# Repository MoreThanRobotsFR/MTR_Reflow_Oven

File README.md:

# MTR Reflow Oven

**MTR Reflow Oven** is a comprehensive hardware and firmware project designed to control a reflow oven for PCB assembly. This repository contains the custom PCB design, the firmware for the RP2040 microcontroller, and a companion PC configurator tool.

## Repository Structure

*   **`Firmware/`**
    *   **`mtr_reflow_oven/`**: The core C++ firmware for the RP2040 microcontroller. It handles temperature PID control, user interface (LVGL), and profile management.
    *   **`Configurator/`**: A Python-based desktop application for creating and managing reflow profiles and configuring device settings.
*   **`Hardware/`**
    *   Contains the KiCad project files (`.kicad_pcb`, `.kicad_sch`) for the custom controller board.

## Getting Started

### Hardware
The `Hardware` directory contains the complete KiCad project. You can open `Hardware/MTR_Reflow_Oven.kicad_pro` with [KiCad 8.0+](https://www.kicad.org/) to view or modify the schematics and PCB layout.

### Firmware (RP2040)
The firmware is built using the Raspberry Pi Pico SDK.

**Prerequisites:**
*   CMake
*   Arm GNU Toolchain (`arm-none-eabi-gcc`)
*   Pico SDK

**Build Instructions:**
1.  Navigate to the firmware directory:
    ```bash
    cd Firmware/mtr_reflow_oven
    ```
2.  Create a build directory:
    ```bash
    mkdir build
    cd build
    ```
3.  Configure and build:
    ```bash
    cmake ..
    make
    ```
4.  Flash the resulting `.uf2` file to your RP2040 device.

### Configurator (PC Software)
The configurator allows you to easily edit reflow profiles.

**Prerequisites:**
*   Python 3.x
*   Required packages (see `requirements.txt` if available, or manually install common dependencies like `pyserial`, `tkinter`/`customtkinter`).

**Running:**
```bash
cd Firmware/Configurator
python reflow_configurator.py
```

## License
[License Information Here]

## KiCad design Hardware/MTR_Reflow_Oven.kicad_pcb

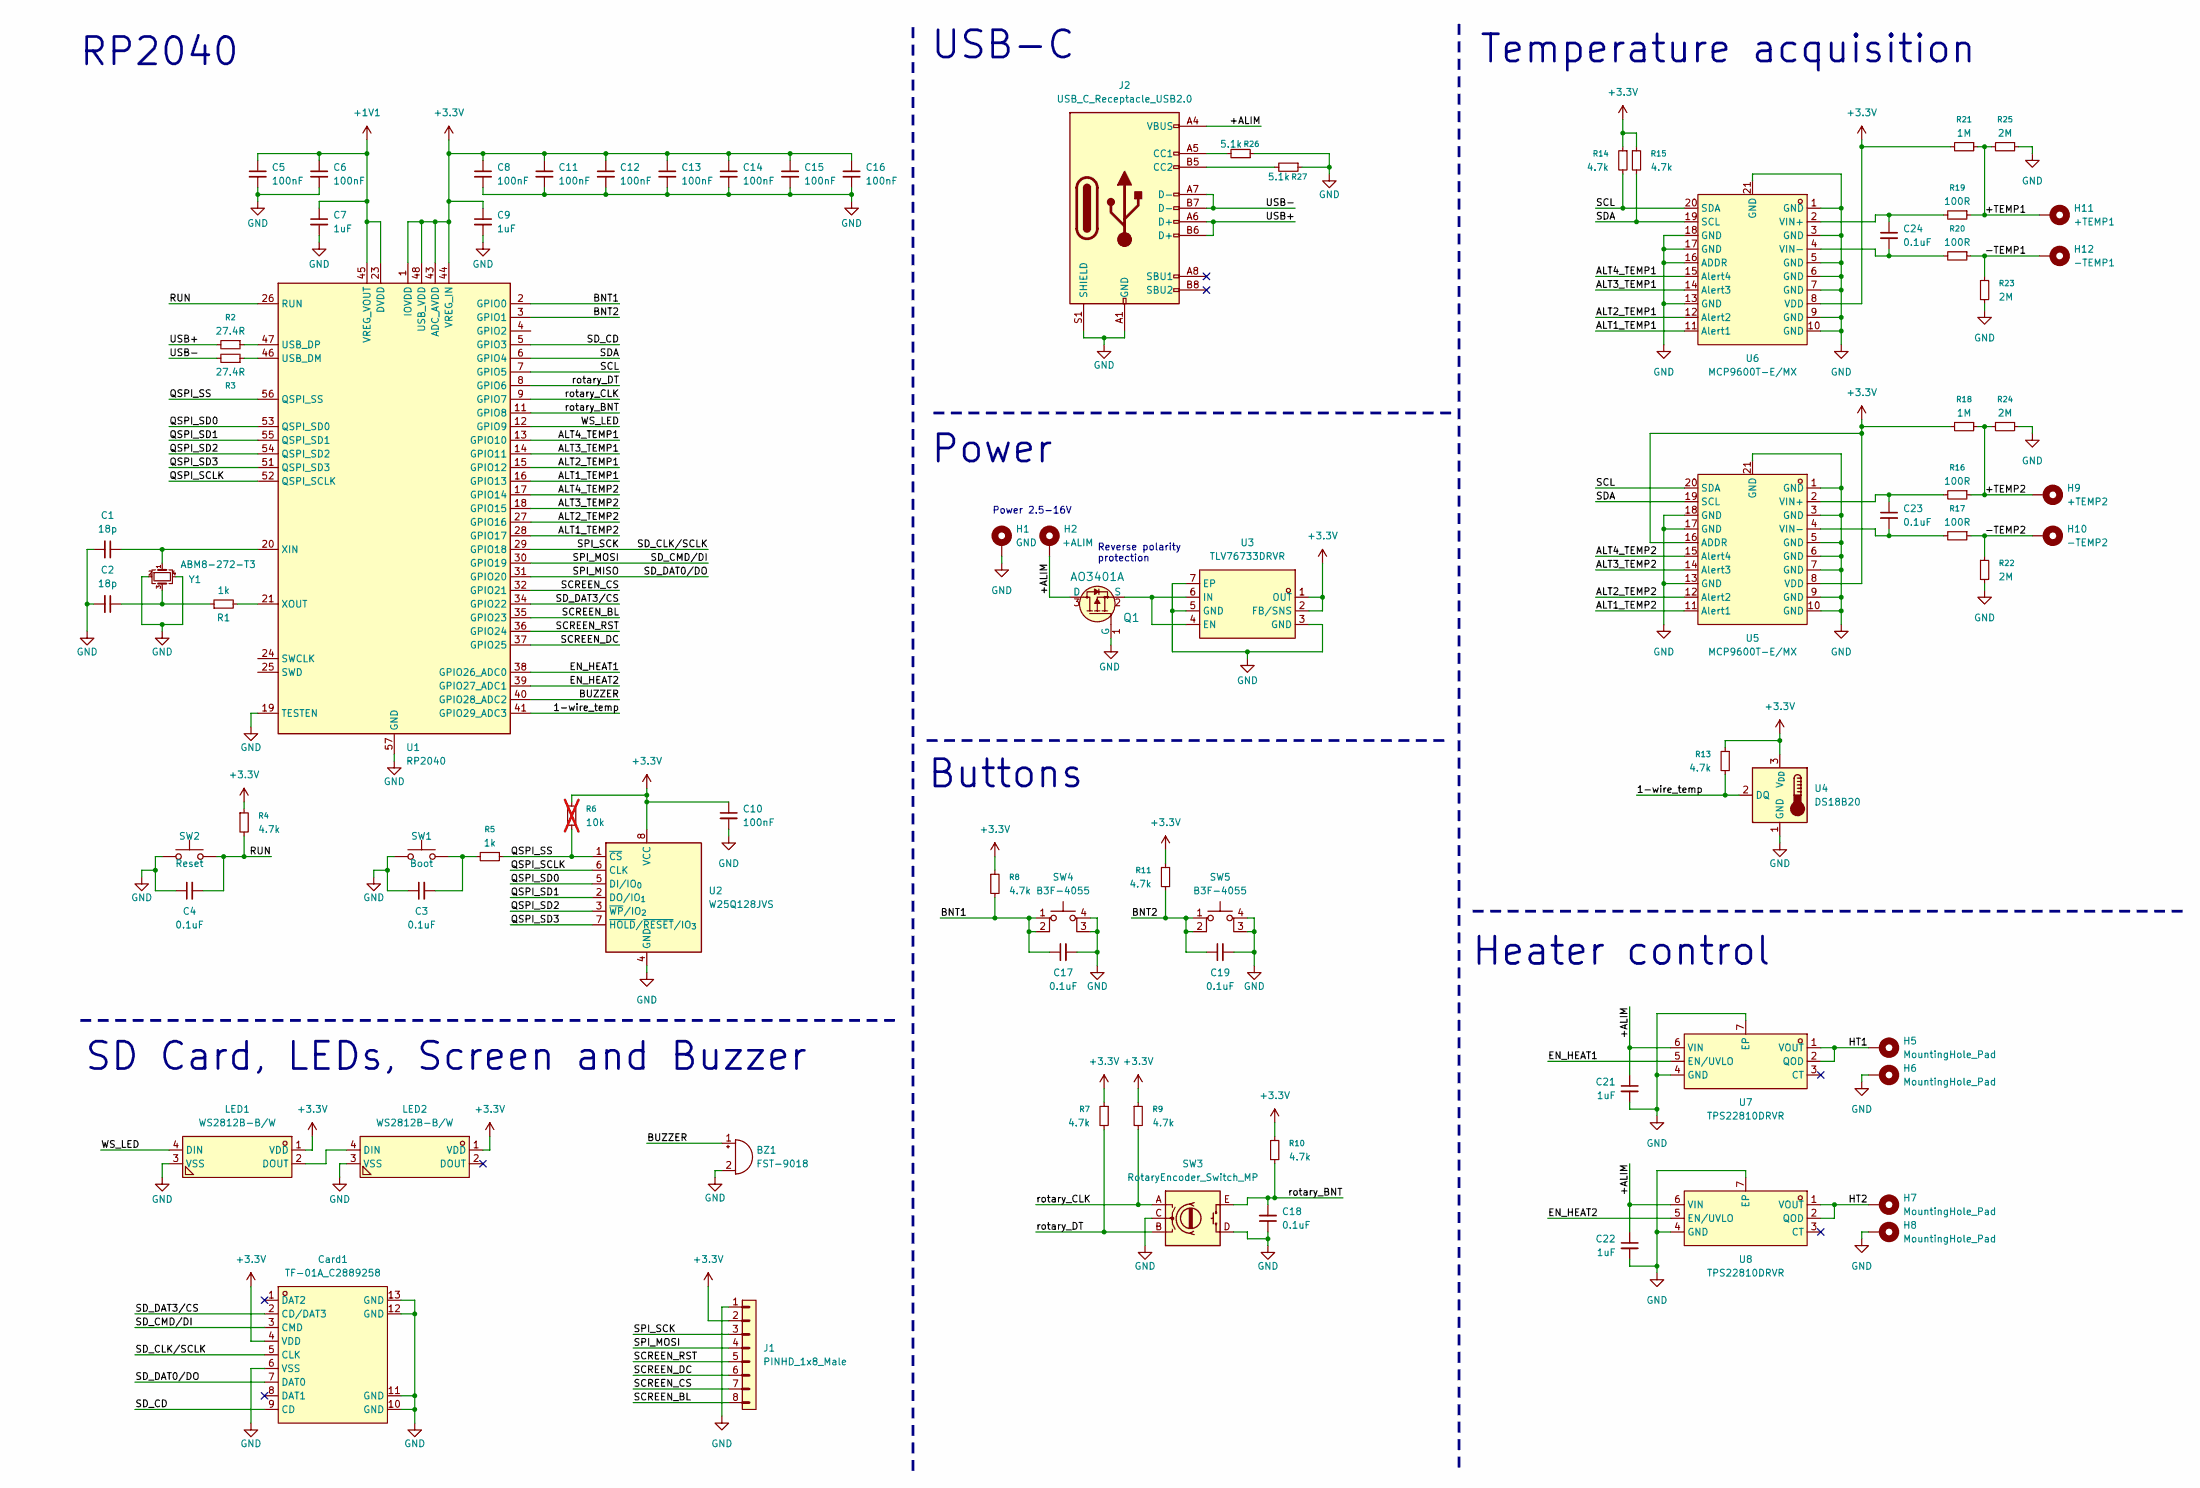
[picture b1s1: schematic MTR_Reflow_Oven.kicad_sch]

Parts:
BZ1: FST-9018; BUZ-SMD_FST-9018; LCSC Part C391035
C1, C2: 18p; C_0402_1005Metric; LCSC C33149
C3, C4, C17, C18, C19: 0.1uF; R_0402_1005Metric; LCSC C60474
C5, C6, C8, C10, C11, C12, C13, C14, C15, C16: 100nF; C_0402_1005Metric; LCSC C1525
C7, C9, C21, C22: 1uF; C_0402_1005Metric; LCSC C14445
C23, C24: 0.1uF; C_0402_1005Metric; LCSC C60474
Card1: TF-01A_C2889258; TF-SMD_TF-02; LCSC Part C2889258
H1: GND; MountingHole_2.2mm_M2_Pad
H2: +ALIM; MountingHole_2.2mm_M2_Pad
H5, H6, H7, H8: MountingHole_Pad; MountingHole_2.2mm_M2_Pad
H9: +TEMP2; MountingHole_2.2mm_M2_Pad
H10: -TEMP2; MountingHole_2.2mm_M2_Pad
H11: +TEMP1; MountingHole_2.2mm_M2_Pad
H12: -TEMP1; MountingHole_2.2mm_M2_Pad
J1: PINHD_1x8_Male; PinHeader_1x08_P2.54mm_Vertical
J2: USB_C_Receptacle_USB2.0; USB_C_Receptacle_HRO_TYPE-C-31-M-12; LCSC C165948
LED1, LED2: WS2812B-B/W; LED-SMD_4P-L5.0-W5.0-TL_WS2812B-B; LCSC Part C2761795
Q1: AO3401A; SOT-23-3; MPN AO3401A; Digi-Key_PN 785-1001-1-ND
R1, R5: 1k; R_0402_1005Metric; LCSC C106235
R2, R3: 27.4R; R_0402_1005Metric; LCSC C31439
R4, R7, R8, R9, R10, R11, R13, R14, R15: 4.7k; R_0402_1005Metric; LCSC C105871
R6: 10k; R_0402_1005Metric; LCSC C60490; not fitted
R16, R17, R19, R20: 100R; R_0402_1005Metric; LCSC C106232
R18, R21: 1M; R_0402_1005Metric; LCSC C138033
R22, R23, R24, R25: 2M; R_0402_1005Metric; LCSC C11512
R26, R27: 5.1k; R_0402_1005Metric; LCSC C105871
SW1: Boot; SW-SMD_L4.0-W3.0-LS5.0; LCSC C2888420
SW2: Reset; SW-SMD_L4.0-W3.0-LS5.0; LCSC C2888420
SW3: RotaryEncoder_Switch_MP; SW-TH_EC11XXXXXXXX; LCSC C470742
SW4, SW5: B3F-4055; KEY-TH_4P-L12.0-W12.0-P5.00-LS13.4-EH; LCSC C84931
U1: RP2040; QFN-56-1EP_7x7mm_P0.4mm_EP3.2x3.2mm_ThermalVias; LCSC C2040
U2: W25Q128JVS; SOIC-8_5.3x5.3mm_P1.27mm; LCSC C97521
U3: TLV76733DRVR; WSON-6_L2.0-W2.0-P0.65-TL-EP; LCSC Part C2848334
U4: DS18B20; TO-92_Inline; LCSC C9753
U5, U6: MCP9600T-E/MX; QFN-20-1EP_5x5mm_P0.65mm_EP3.35x3.35mm_ThermalVias; LCSC Part C623918
U7, U8: TPS22810DRVR; WSON-6-1EP_2x2mm_P0.65mm_EP1x1.6mm; LCSC Part C527679
Y1: ABM8-272-T3; CRYSTAL-SMD_4P-L3.2-W2.5-BL; LCSC C20625731

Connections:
+1V1: C5.1, C6.1, C7.1, U1.23 (DVDD), U1.45 (VREG_VOUT), U1.50 (DVDD)
+3.3V: C8.1, C9.1, C10.1, C11.1, C12.1, C13.1, C14.1, C15.1, C16.1, Card1.4 (VDD), J1.2, LED1.1 (VDD), LED2.1 (VDD), R4.1, R6.1, R7.1, R8.1, R9.1, R10.1, R11.1, R13.1, R14.1, R15.1, R18.2, R21.2, U1.1 (IOVDD), U1.10 (IOVDD), U1.22 (IOVDD), U1.33 (IOVDD), U1.42 (IOVDD), U1.43 (ADC_AVDD), U1.44 (VREG_IN), U1.48 (USB_VDD), U1.49 (IOVDD), U2.8 (VCC), U3.1 (OUT), U3.2 (FB/SNS), U4.3 (V_{DD}), U5.8 (VDD), U5.16 (ADDR), U6.8 (VDD)
/1-wire_temp: R13.2, U1.41 (GPIO29_ADC3), U4.2 (DQ)
/+ALIM: C21.1, C22.1, H2.1, J2.A4 (VBUS), J2.A9 (VBUS), J2.B4 (VBUS), J2.B9 (VBUS), Q1.3 (D), U7.6 (VIN), U8.6 (VIN)
/+TEMP1: H11.1, R19.1, R21.1, R25.2
/+TEMP2: H9.1, R16.1, R18.1, R24.2
/-TEMP1: H12.1, R20.1, R23.1
/-TEMP2: H10.1, R17.1, R22.1
/ALT1_TEMP1: U1.16 (GPIO13), U6.11 (Alert1)
/ALT1_TEMP2: U1.28 (GPIO17), U5.11 (Alert1)
/ALT2_TEMP1: U1.15 (GPIO12), U6.12 (Alert2)
/ALT2_TEMP2: U1.27 (GPIO16), U5.12 (Alert2)
/ALT3_TEMP1: U1.14 (GPIO11), U6.14 (Alert3)
/ALT3_TEMP2: U1.18 (GPIO15), U5.14 (Alert3)
/ALT4_TEMP1: U1.13 (GPIO10), U6.15 (Alert4)
/ALT4_TEMP2: U1.17 (GPIO14), U5.15 (Alert4)
/BNT1: C17.1, R8.2, SW4.1, SW4.2, U1.2 (GPIO0)
/BNT2: C19.1, R11.2, SW5.1, SW5.2, U1.3 (GPIO1)
/BUZZER: BZ1.1 (+), U1.40 (GPIO28_ADC2)
/EN_HEAT1: U1.38 (GPIO26_ADC0), U7.5 (EN/UVLO)
/EN_HEAT2: U1.39 (GPIO27_ADC1), U8.5 (EN/UVLO)
/HT1: H5.1, U7.1 (VOUT), U7.2 (QOD)
/HT2: H7.1, U8.1 (VOUT), U8.2 (QOD)
/QSPI_SCLK: U1.52 (QSPI_SCLK), U2.6 (CLK)
/QSPI_SD0: U1.53 (QSPI_SD0), U2.5 (DI/IO_{0})
/QSPI_SD1: U1.55 (QSPI_SD1), U2.2 (DO/IO_{1})
/QSPI_SD2: U1.54 (QSPI_SD2), U2.3 (~WP/IO_{2})
/QSPI_SD3: U1.51 (QSPI_SD3), U2.7 (~HOLD/~RESET/IO_{3})
/QSPI_SS: R5.1, R6.2, U1.56 (QSPI_SS), U2.1 (~CS)
/RUN: C4.2, R4.2, SW2.2, U1.26 (RUN)
/SCL: R14.2, U1.7 (GPIO5), U5.20 (SDA), U6.20 (SDA)
/SCREEN_BL: J1.8, U1.35 (GPIO23)
/SCREEN_CS: J1.7, U1.32 (GPIO21)
/SCREEN_DC: J1.6, U1.37 (GPIO25)
/SCREEN_RST: J1.5, U1.36 (GPIO24)
/SDA: R15.2, U1.6 (GPIO4), U5.19 (SCL), U6.19 (SCL)
/SD_CD: Card1.9 (CD), U1.5 (GPIO3)
/SD_CLK/SCLK: Card1.5 (CLK), J1.3, U1.29 (GPIO18)
/SD_CMD/DI: Card1.3 (CMD), J1.4, U1.30 (GPIO19)
/SD_DAT0/DO: Card1.7 (DAT0), U1.31 (GPIO20)
/SD_DAT3/CS: Card1.2 (CD/DAT3), U1.34 (GPIO22)
/USB+: J2.A6 (D+), J2.B6 (D+), R2.2
/USB-: J2.A7 (D-), J2.B7 (D-), R3.2
/WS_LED: LED1.4 (DIN), U1.12 (GPIO9)
/rotary_BNT: C18.2, R10.2, SW3.E (S1), U1.11 (GPIO8)
/rotary_CLK: R9.2, SW3.A, U1.9 (GPIO7)
/rotary_DT: R7.2, SW3.B, U1.8 (GPIO6)
GND: BZ1.2 (-), C1.2, C2.2, C3.1, C4.1, C5.2, C6.2, C7.2, C8.2, C9.2, C10.2, C11.2, C12.2, C13.2, C14.2, C15.2, C16.2, C17.2, C18.1, C19.2, C21.2, C22.2, Card1.6 (VSS), Card1.10 (GND), Card1.11 (GND), Card1.12 (GND), Card1.13 (GND), H1.1, H6.1, H8.1, J1.1, J2.A1 (GND), J2.A12 (GND), J2.B1 (GND), J2.B12 (GND), J2.S1 (SHIELD), LED1.3 (VSS), LED2.3 (VSS), Q1.1 (G), R22.2, R23.2, R24.1, R25.1, R26.1, R27.1, SW1.1, SW2.1, SW3.C, SW3.D (S2), SW4.3 (K), SW4.4 (A), SW5.3 (K), SW5.4 (A), U1.19 (TESTEN), U1.57 (GND), U2.4 (GND), U3.3 (GND), U3.5 (GND), U3.7 (EP), U4.1 (GND), U5.1 (GND), U5.3 (GND), U5.5 (GND), U5.6 (GND), U5.7 (GND), U5.9 (GND), U5.10 (GND), U5.13 (GND), U5.17 (GND), U5.18 (GND), U5.21 (GND), U6.1 (GND), U6.3 (GND), U6.5 (GND), U6.6 (GND), U6.7 (GND), U6.9 (GND), U6.10 (GND), U6.13 (GND), U6.16 (ADDR), U6.17 (GND), U6.18 (GND), U6.21 (GND), U7.4 (GND), U7.7 (EP), U8.4 (GND), U8.7 (EP), Y1.2, Y1.4
unnamed: C2.1, R1.1, Y1.3
unnamed: C3.2, R5.2, SW1.2
unnamed: J2.A5 (CC1), R26.2
unnamed: J2.B5 (CC2), R27.2
unnamed: LED1.2 (DOUT), LED2.4 (DIN)
unnamed: Q1.2 (S), U3.4 (EN), U3.6 (IN)
unnamed: R3.1, U1.46 (USB_DM)
unnamed: R2.1, U1.47 (USB_DP)
unnamed: C1.1, U1.20 (XIN), Y1.1
unnamed: R1.2, U1.21 (XOUT)
unnamed: C23.1, R16.2, U5.2 (VIN+)
unnamed: C23.2, R17.2, U5.4 (VIN-)
unnamed: C24.1, R19.2, U6.2 (VIN+)
unnamed: C24.2, R20.2, U6.4 (VIN-)

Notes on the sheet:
Power
Temperature acquisition
USB-C
Heater control
SD Card, LEDs, Screen and Buzzer
Reverse polarity protection
Buttons
Power 2.5-16V
RP2040

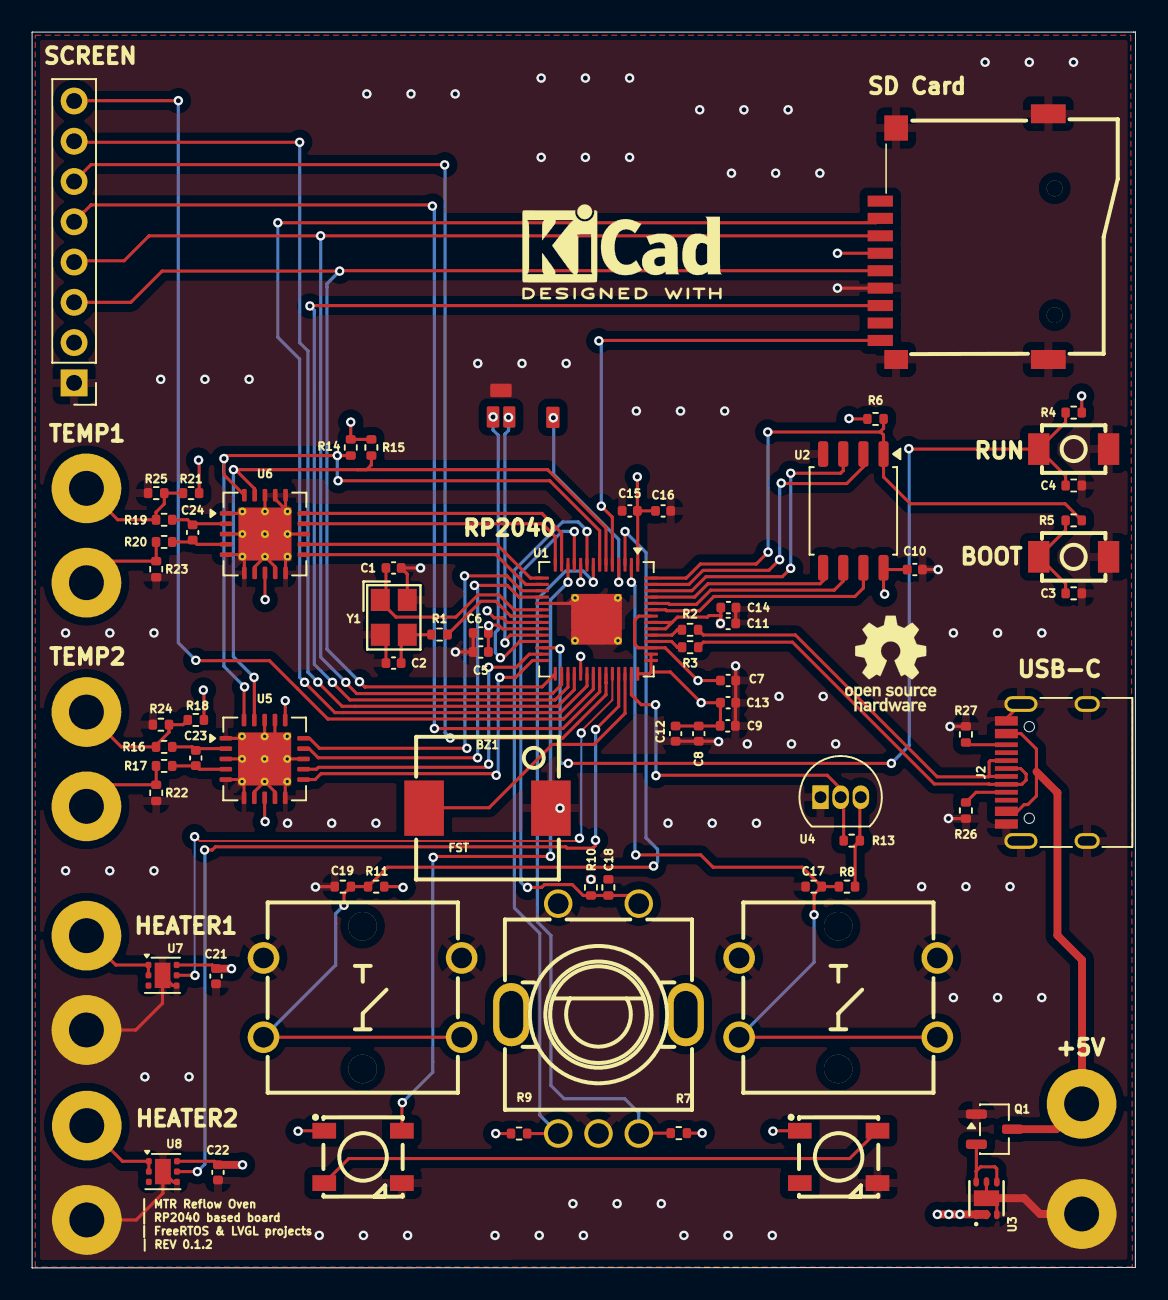
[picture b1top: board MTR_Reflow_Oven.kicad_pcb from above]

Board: 4 copper layers, 69.6 x 77.9 mm, 80 parts (0 on the bottom side), 62 nets.

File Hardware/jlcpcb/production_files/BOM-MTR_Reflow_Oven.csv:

Comment,Designator,Footprint,LCSC,Quantity
0.1uF,"C17,C18,C19,C23,C24,C3,C4",R_0402_1005Metric,C60474,7
100R,"R16,R17,R19,R20",R_0402_1005Metric,C106232,4
100nF,"C10,C11,C12,C13,C14,C15,C16,C5,C6,C8",C_0402_1005Metric,C1525,10
10k,,R_0402_1005Metric,C60490,0
18p,"C1,C2",C_0402_1005Metric,C33149,2
1M,"R18,R21",R_0402_1005Metric,C138033,2
1k,"R1,R5",R_0402_1005Metric,C106235,2
1uF,"C21,C22,C7,C9",C_0402_1005Metric,C14445,4
27.4R,"R2,R3",R_0402_1005Metric,C31439,2
2M,"R22,R23,R24,R25",R_0402_1005Metric,C11512,4
4.7k,"R10,R11,R13,R14,R15,R4,R7,R8,R9",R_0402_1005Metric,C105871,9
5.1k,"R26,R27",R_0402_1005Metric,C105871,2
ABM8-272-T3,Y1,CRYSTAL-SMD_4P-L3.2-W2.5-BL,C20625731,1
AO3401A,Q1,SOT-23-3,C15127,1
B3F-4055,"SW4,SW5",KEY-TH_4P-L12.0-W12.0-P5.00-LS13.4-EH,C84931,2
Boot,SW1,SW-SMD_L4.0-W3.0-LS5.0,C2888420,1
DS18B20,U4,TO-92_Inline,C9753,1
FST-9018,BZ1,BUZ-SMD_FST-9018,C391035,1
MCP9600T-E/MX,"U5,U6",QFN-20-1EP_5x5mm_P0.65mm_EP3.35x3.35mm_ThermalVias,C623918,2
RP2040,U1,QFN-56-1EP_7x7mm_P0.4mm_EP3.2x3.2mm_ThermalVias,C2040,1
Reset,SW2,SW-SMD_L4.0-W3.0-LS5.0,C2888420,1
RotaryEncoder_Switch_MP,SW3,SW-TH_EC11XXXXXXXX,C470742,1
TF-01A_C2889258,Card1,TF-SMD_TF-02,C2889258,1
TLV76733DRVR,U3,WSON-6_L2.0-W2.0-P0.65-TL-EP,C2848334,1
TPS22810DRVR,"U7,U8",WSON-6-1EP_2x2mm_P0.65mm_EP1x1.6mm,C527679,2
USB_C_Receptacle_USB2.0,J2,USB_C_Receptacle_HRO_TYPE-C-31-M-12,C165948,1
W25Q128JVS,U2,SOIC-8_5.3x5.3mm_P1.27mm,C97521,1
WS2812B-B/W,"LED1,LED2",LED-SMD_4P-L5.0-W5.0-TL_WS2812B-B,C2761795,2
PINHD_1x8_Male,J1,PinHeader_1x08_P2.54mm_Vertical,,1

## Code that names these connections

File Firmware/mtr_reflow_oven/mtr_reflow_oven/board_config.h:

#ifndef BOARD_CONFIG_H
#define BOARD_CONFIG_H

// --- Inputs (Control Panel) ---
#define GPIO_BTN1      0  // Input (Confirm/Start)
#define GPIO_BTN2      1  // Input (Stop/Back)

#define GPIO_SD_CD     3  // Input (SD Card Detect)

// --- I2C Bus (Sensors) ---
#define GPIO_I2C_SDA   4
#define GPIO_I2C_SCL   5
#define I2C_PORT       i2c0
#define I2C_ADDR_MCP9600_T1 0x60 // Default address for Sensor 1
#define I2C_ADDR_MCP9600_T2 0x67 // Default address for Sensor 2 (if present)

// --- Rotary Encoder ---
#define GPIO_ROT_DT    6
#define GPIO_ROT_CLK   7
#define GPIO_ROT_BTN   8

// --- Status LEDs ---
#define GPIO_WS_LED    9  // WS2812B Data

// --- MCP9600 Alerts (Sensor 1) ---
#define GPIO_T1_ALT4   10
#define GPIO_T1_ALT3   11
#define GPIO_T1_ALT2   12
#define GPIO_T1_ALT1   13

// --- MCP9600 Alerts (Sensor 2) ---
#define GPIO_T2_ALT4   14
#define GPIO_T2_ALT3   15
#define GPIO_T2_ALT2   16
#define GPIO_T2_ALT1   17

// --- SPI Bus (Screen + SD) ---
#define GPIO_SPI_SCK   18
#define GPIO_SPI_MOSI  19
#define GPIO_SPI_MISO  20
#define SPI_PORT       spi0

// --- Chip Selects & Control ---
#define GPIO_SCR_CS    21
#define GPIO_SD_CS     22
#define GPIO_SCR_BL    23 // PWM
#define GPIO_SCR_RST   24
#define GPIO_SCR_DC    25

// --- Power Outputs (SSRs) ---
#define GPIO_HEAT1     26 // PWM (SSR 1)
#define GPIO_HEAT2     27 // PWM (SSR 2)

// --- Audio ---
#define GPIO_BUZZER    28 // PWM

// --- 1-Wire ---
#define GPIO_ONE_WIRE  29


#endif // BOARD_CONFIG_H

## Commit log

2026-01-31 Add README.md
2026-05-18 Enable RP2040 dual-core and add README
    Set FreeRTOS SMP core count to 2 for the RP2040 SMP port (configNUMBER_OF_CORES changed from 1 to 2) so the firmware can run on both cores. Add a new README.md documenting the MTR Reflow Oven firmwar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
